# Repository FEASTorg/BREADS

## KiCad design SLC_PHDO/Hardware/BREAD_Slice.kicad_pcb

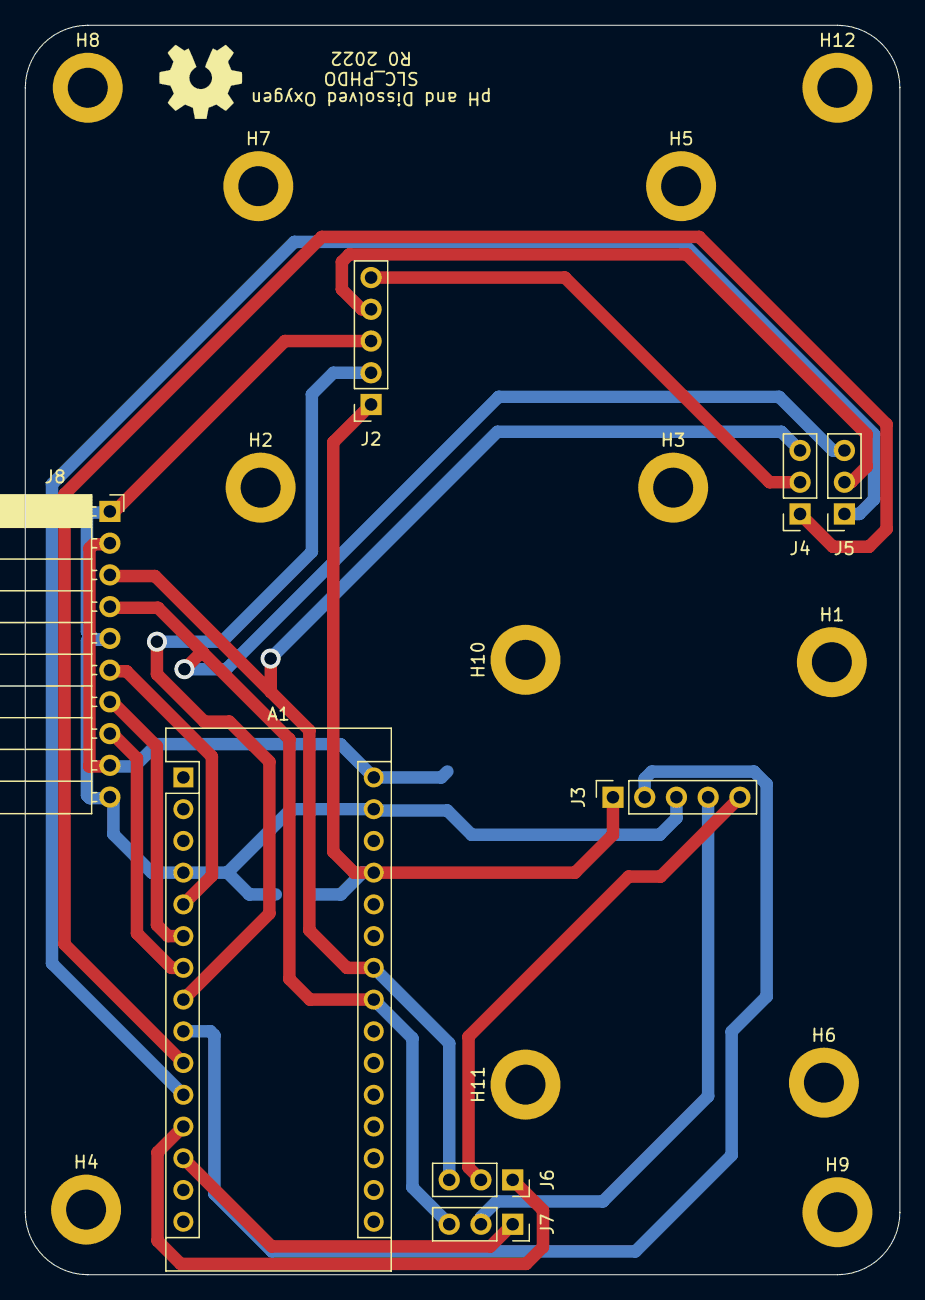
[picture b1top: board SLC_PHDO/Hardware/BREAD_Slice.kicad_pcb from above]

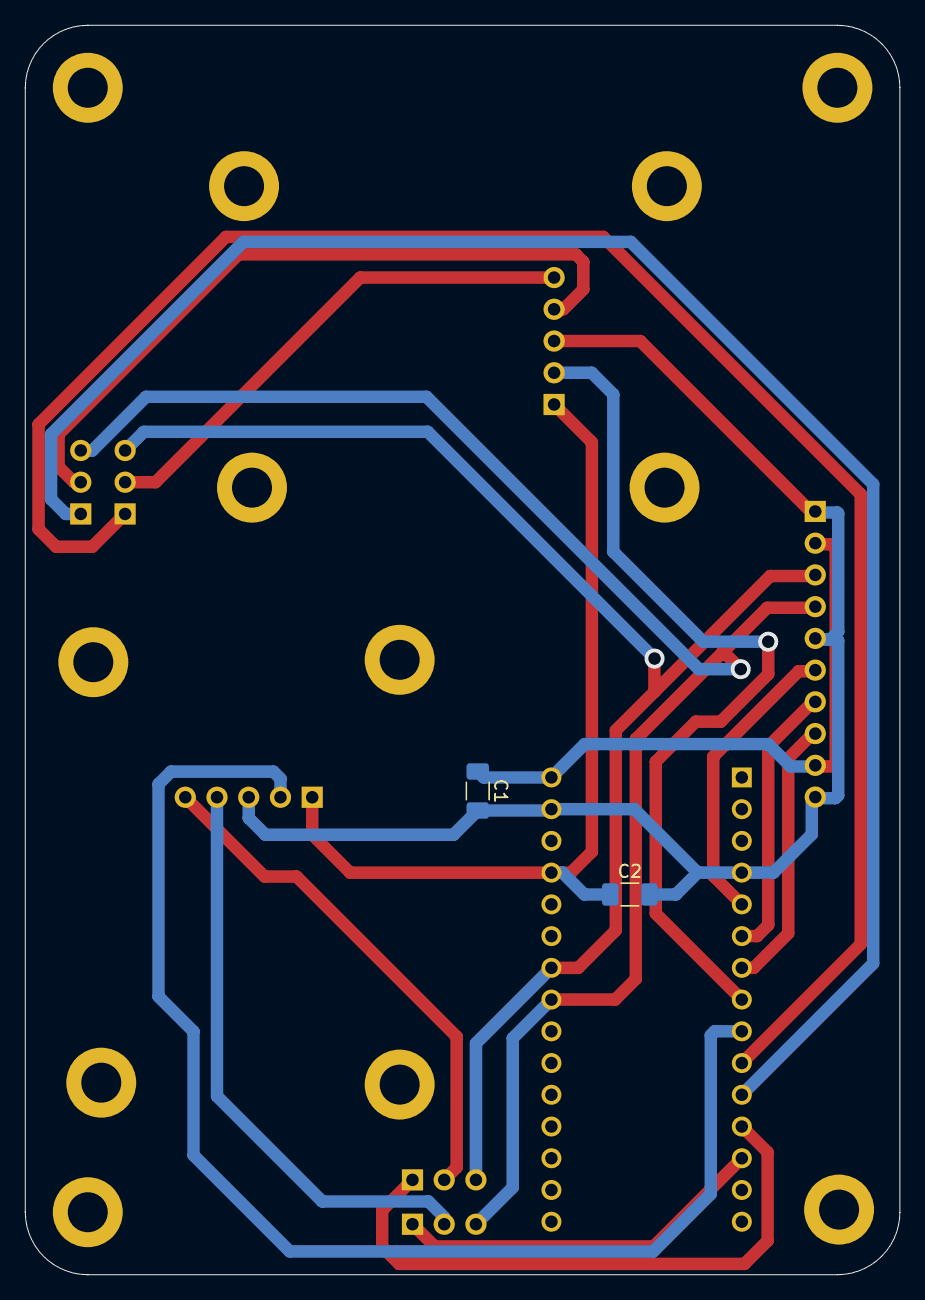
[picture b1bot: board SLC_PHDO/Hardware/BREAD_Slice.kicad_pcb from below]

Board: 2 copper layers, 70.0 x 100.0 mm, 23 parts (2 on the bottom side), 15 nets.

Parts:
A1: Arduino_Nano_v3.x; Arduino_Nano
C1, C2: 10uF_t; C_1206_3216Metric_Pad1.33x1.80mm_HandSolder
H1, H2, H3, H4, H5, H6, H7, H8, H9, H10, H11, H12: MountingHole; MountingHole_3.2mm_M3_DIN965_Pad
J2, J3: Conn_01x05_Female; PinSocket_1x05_P2.54mm_Vertical
J4, J5, J6, J7: Conn_01x03_Male; PinSocket_1x03_P2.54mm_Vertical
J8: Conn_01x10_Female; PinSocket_1x10_P2.54mm_Horizontal
Logo1: Logo_Open_Hardware_Small; OSHW-Symbol_6.7x6mm_SilkScreen

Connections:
+5V: A1.27 (+5V), C2.1, J2.1, J3.1
+12V: A1.30 (VIN), C1.1, J8.2, J8.9
/I2C_CLK: A1.24 (A5), J4.3, J6.3
/I2C_DAT: A1.23 (A4), J5.3, J7.3
/OFFO2: A1.8 (D5), J2.2
/OFFpH: A1.9 (D6), J3.2
/RX1: A1.10 (D7), J4.1
/RX1/SCL: J2.5, J4.2
/RX2: A1.12 (D9), J6.1
/RX2/SCL: J3.5, J6.2
/TX1: A1.11 (D8), J5.1
/TX1/SDA: J2.4, J5.2
/TX2: A1.13 (D10), J7.1
/TX2/SDA: J3.4, J7.2
GND: A1.4 (GND), A1.29 (GND), C1.2, C2.2, J2.3, J3.3, J8.1, J8.5, J8.10

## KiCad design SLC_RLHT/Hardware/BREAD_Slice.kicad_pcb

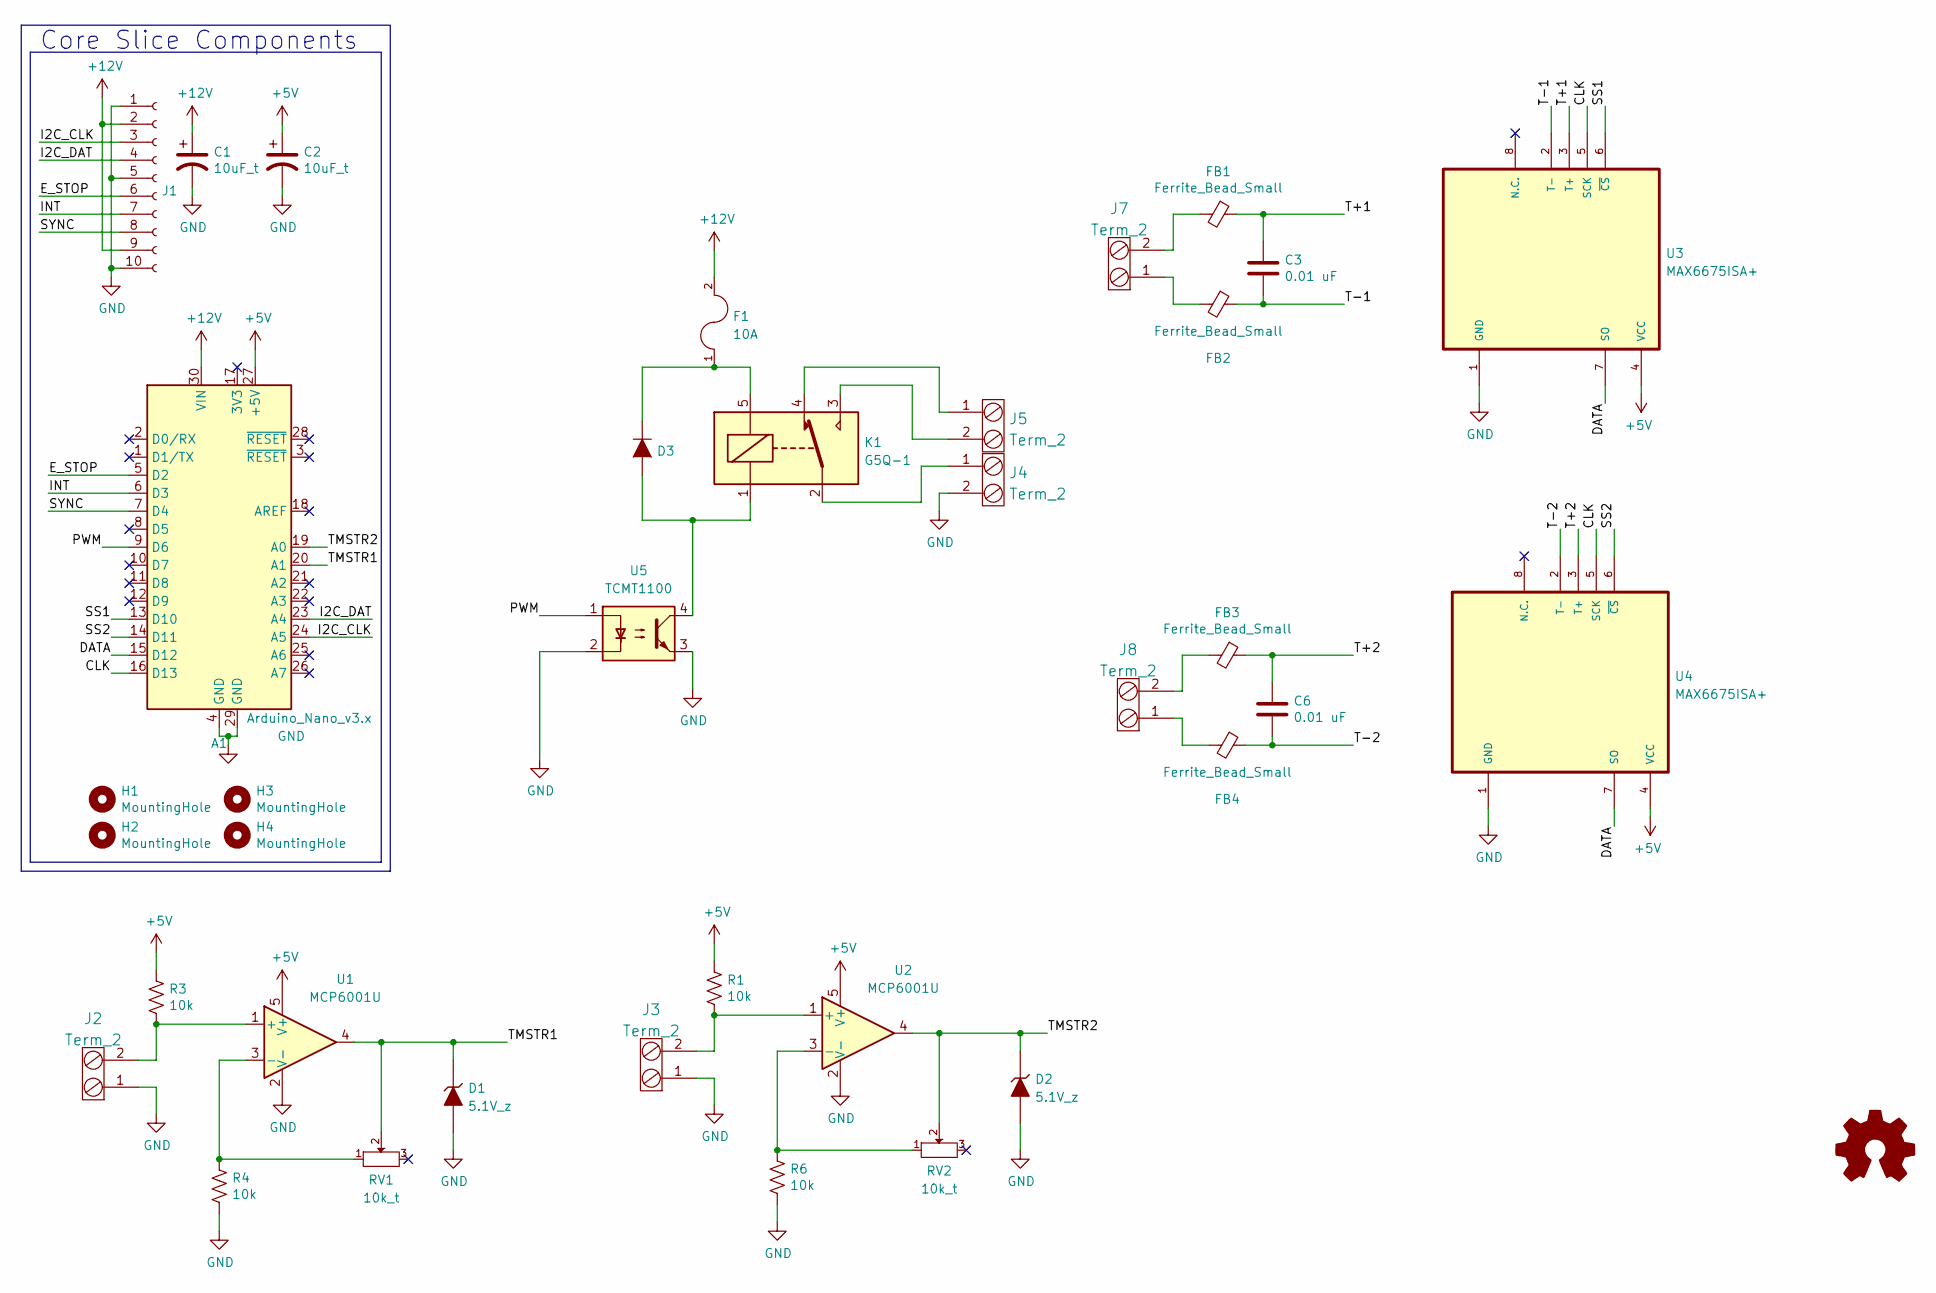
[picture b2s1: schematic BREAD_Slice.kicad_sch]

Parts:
A1: Arduino_Nano_v3.x; Arduino_Nano
C1, C2: 10uF_t; C_1206_HandSoldering; Part # T491C106K025AT
C3, C6: 0.01 uF; C_1206_HandSoldering
D1, D2: 5.1V_z; Diode_DO-41_SOD81_Horizontal_RM10; Part # 1N4733ATR
D3: General_Purpose_Diode; Diode_DO-201AD_Horizontal_RM15; Part # 1N914BWS
F1: 10A; Fuse_Holder; Part # 3522-2
FB1, FB2, FB3, FB4: Ferrite_Bead_Small; R_1206_HandSoldering
H1, H2, H3, H4: MountingHole; MountingHole_3.2mm_M3_DIN965_Pad
J1: Conn_01x10_Female; PinSocket_1x10_P2.54mm_Horizontal
J2, J3, J4, J5, J7, J8: Term_2; TerminalBlock_Pheonix_MKDS1.5-2pol; Part # 1935161
K1: G5Q-1; Relay_SPDT_Omron-G5Q-1
Logo1: Logo_Open_Hardware_Small; OSHW-Symbol_6.7x6mm_SilkScreen
R1, R3, R4, R6: 10k; R_1206_HandSoldering
RV1, RV2: 10k_t; Potentiometer_Bourns_3296W_3-8Zoll_Inline_ScrewUp; Part # 1-1623849-0
U1, U2: MCP6001U; SOT-23-5
U3, U4: MAX6675ISA+; SOIC127P600X175-8N
U5: TCMT1100; SOP-4_4.4x2.6mm_P1.27mm

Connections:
+5V: A1.27 (+5V), C2.1, R1.1, R3.1, U1.5 (V+), U2.5 (V+), U3.4 (VCC), U4.4 (VCC)
+12V: A1.30 (VIN), C1.1, F1.2, J1.2, J1.9
/CLK: A1.16 (D13), U3.5 (SCK), U4.5 (SCK)
/DATA: A1.15 (D12), U3.7 (SO), U4.7 (SO)
/E_STOP: A1.5 (D2), J1.6
/I2C_CLK: A1.24 (A5), J1.3
/I2C_DAT: A1.23 (A4), J1.4
/INT: A1.6 (D3), J1.7
/PWM: A1.9 (D6), U5.1
/SS1: A1.13 (D10), U3.6 (~CS)
/SS2: A1.14 (D11), U4.6 (~CS)
/SYNC: A1.7 (D4), J1.8
/T+1: C3.1, FB1.1, U3.3 (T+)
/T+2: C6.1, FB3.1, U4.3 (T+)
/T-1: C3.2, FB2.1, U3.2 (T-)
/T-2: C6.2, FB4.1, U4.2 (T-)
/TMSTR1: A1.20 (A1), D1.1 (K), RV1.2, U1.4
/TMSTR2: A1.19 (A0), D2.1 (K), RV2.2, U2.4
GND: A1.4 (GND), A1.29 (GND), C1.2, C2.2, D1.2 (A), D2.2 (A), J1.1, J1.5, J1.10, J2.1, J3.1, J4.2, R4.2, R6.2, U1.2 (V-), U2.2 (V-), U3.1 (GND), U4.1 (GND), U5.2, U5.3
unnamed: D3.1 (K), F1.1, K1.5
unnamed: FB1.2, J7.2
unnamed: FB2.2, J7.1
unnamed: FB3.2, J8.2
unnamed: FB4.2, J8.1
unnamed: J2.2, R3.2, U1.1 (+)
unnamed: J3.2, R1.2, U2.1 (+)
unnamed: J4.1, K1.2
unnamed: J5.1, K1.4
unnamed: J5.2, K1.3
unnamed: D3.2 (A), K1.1, U5.4
unnamed: R4.1, RV1.1, U1.3 (-)
unnamed: R6.1, RV2.1, U2.3 (-)

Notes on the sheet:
Core Slice Components

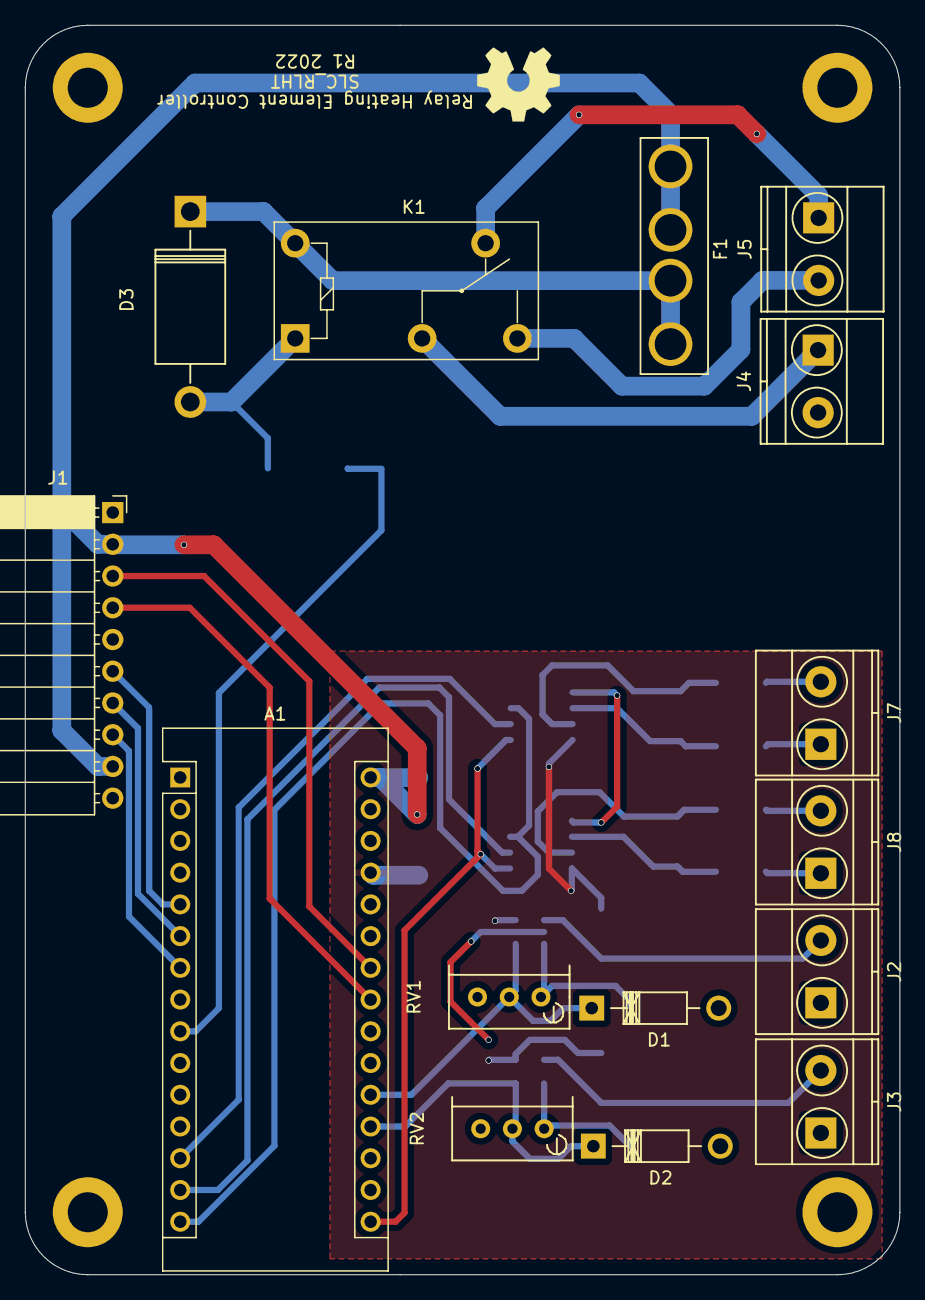
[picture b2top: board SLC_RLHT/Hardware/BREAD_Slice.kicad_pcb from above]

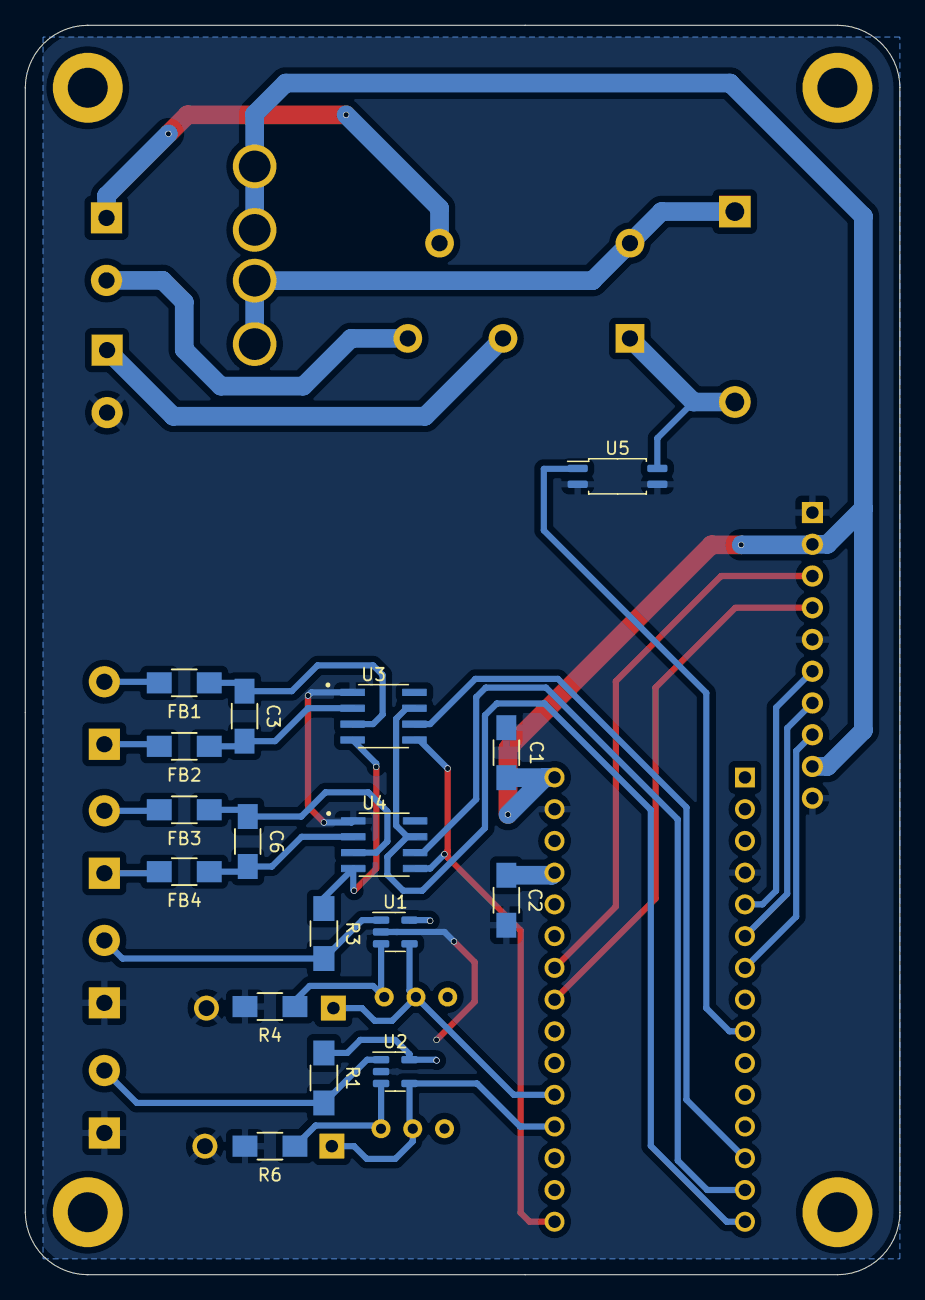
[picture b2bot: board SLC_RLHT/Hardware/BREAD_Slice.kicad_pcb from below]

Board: 2 copper layers, 70.0 x 100.0 mm, 37 parts (17 on the bottom side), 32 nets.

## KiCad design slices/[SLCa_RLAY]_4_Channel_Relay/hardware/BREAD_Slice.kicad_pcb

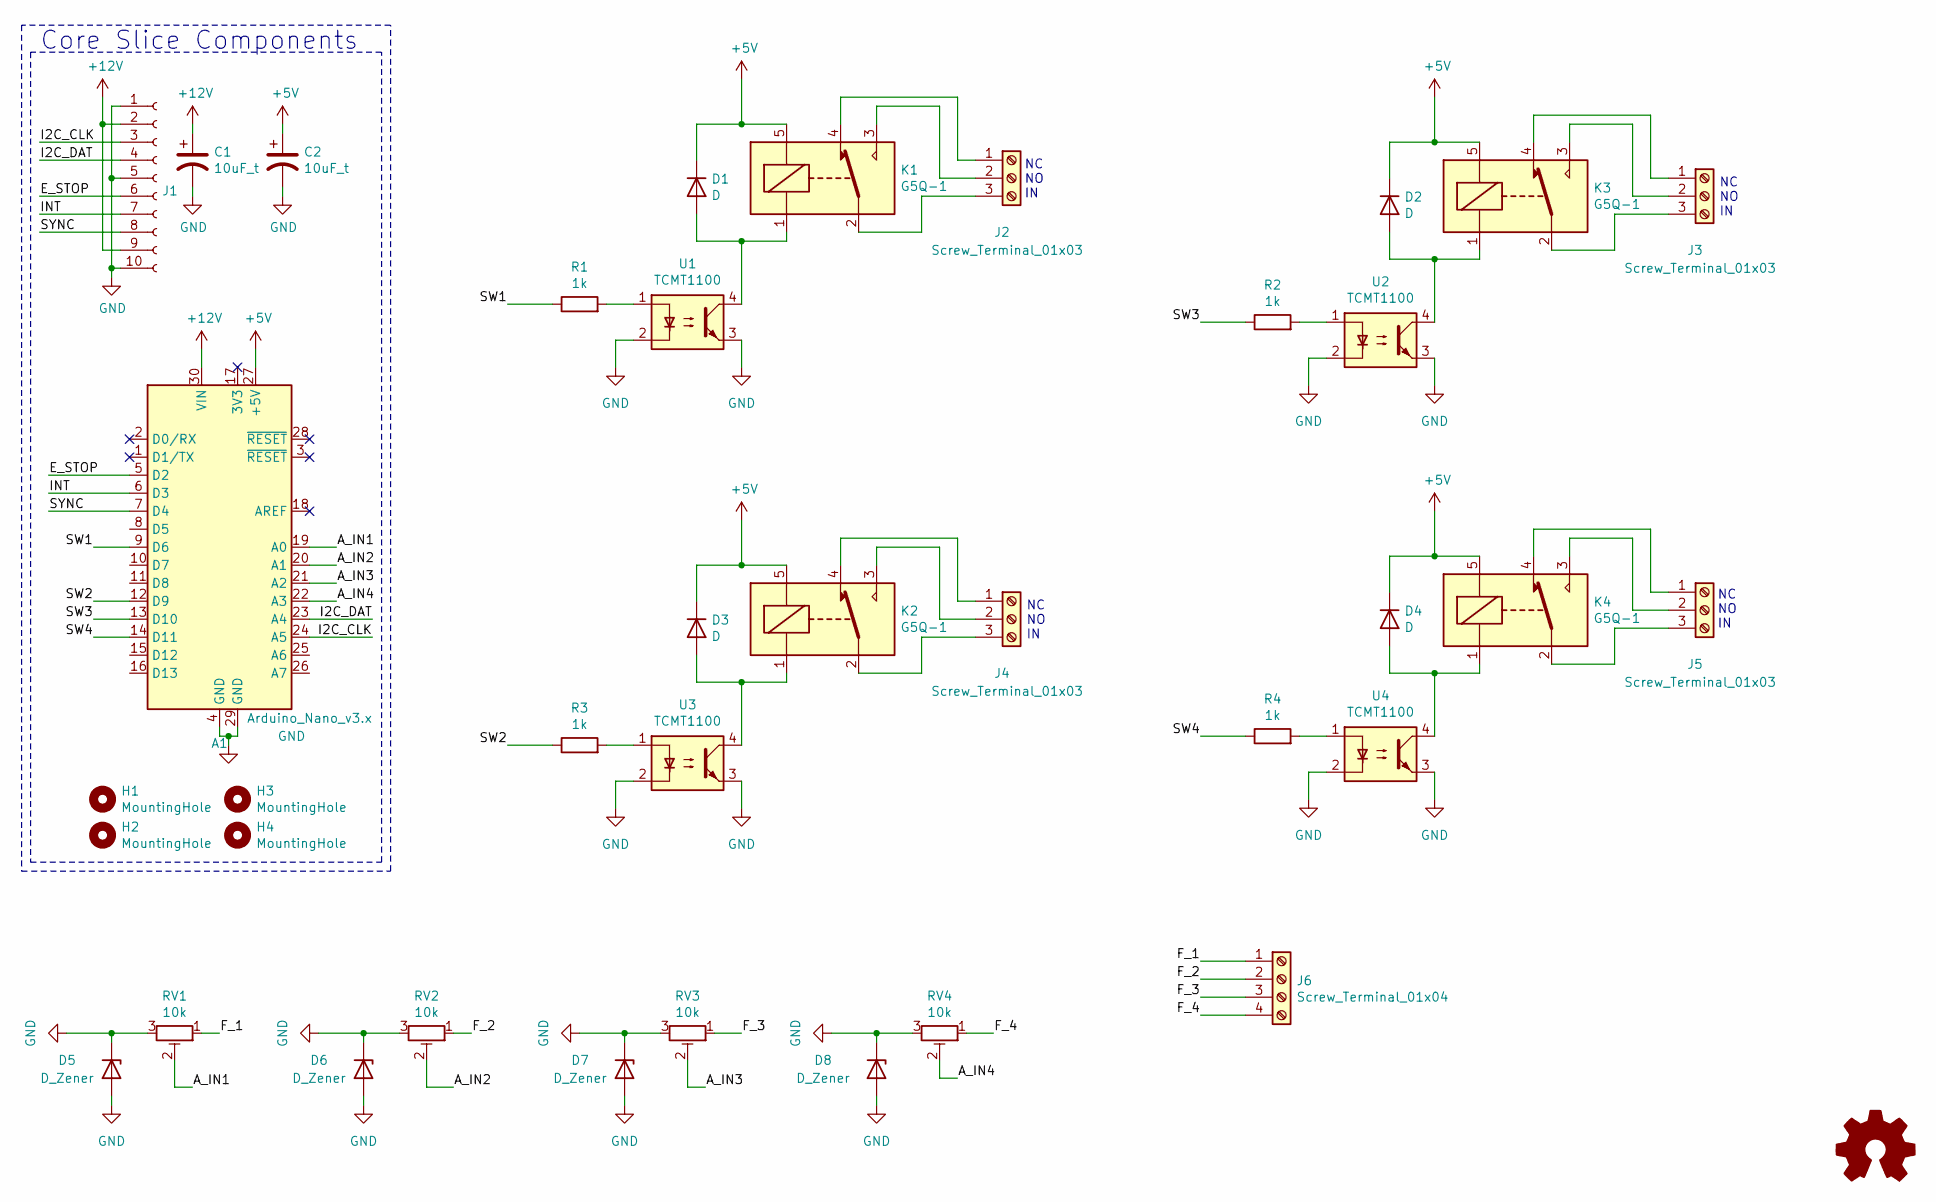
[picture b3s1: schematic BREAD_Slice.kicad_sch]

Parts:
A1: Arduino_Nano_v3.x; Arduino_Nano
C1, C2: 10uF_t; C_2312; Part # T491C106K025AT
D1, D2, D3, D4: D; D_1206_3216Metric_Pad1.42x1.75mm_HandSolder
D5, D6, D7, D8: D_Zener; D_1206_3216Metric_Pad1.42x1.75mm_HandSolder
H1, H2, H3, H4: MountingHole; MountingHole_3.2mm_M3_DIN965_Pad
J1: Conn_01x10_Female; PinSocket_1x10_P2.54mm_Horizontal
J2, J3, J4, J5: Screw_Terminal_01x03; TerminalBlock_TE_282834-3_1x03_P2.54mm_Horizontal
J6: Screw_Terminal_01x04; TerminalBlock_TE_282834-4_1x04_P2.54mm_Horizontal
K1, K2, K3, K4: G5Q-1; Relay_SPDT_Omron-G5Q-1
Logo1: Logo_Open_Hardware_Small; OSHW-Symbol_6.7x6mm_SilkScreen
R1, R2, R3, R4: 1k; R_1206_3216Metric_Pad1.30x1.75mm_HandSolder
RV1, RV2, RV3, RV4: 10k; Potentiometer_Bourns_3266W_Vertical
U1, U2, U3, U4: TCMT1100; SOP-4_4.4x2.6mm_P1.27mm

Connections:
+5V: A1.27 (+5V), C2.1, D1.1 (K), D2.1 (K), D3.1 (K), D4.1 (K), K1.5, K2.5, K3.5, K4.5
+12V: A1.30 (VIN), C1.1, J1.2, J1.9
/A_IN1: A1.19 (A0), RV1.2
/A_IN2: A1.20 (A1), RV2.2
/A_IN3: A1.21 (A2), RV3.2
/A_IN4: A1.22 (A3), RV4.2
/E_STOP: A1.5 (D2), J1.6
/F_1: J6.1, RV1.1
/F_2: J6.2, RV2.1
/F_3: J6.3, RV3.1
/F_4: J6.4, RV4.1
/I2C_CLK: A1.24 (A5), J1.3
/I2C_DAT: A1.23 (A4), J1.4
/INT: A1.6 (D3), J1.7
/SW1: A1.9 (D6), R1.1
/SW2: A1.12 (D9), R3.1
/SW3: A1.13 (D10), R2.1
/SW4: A1.14 (D11), R4.1
/SYNC: A1.7 (D4), J1.8
GND: A1.4 (GND), A1.29 (GND), C1.2, C2.2, D5.1 (K), D5.2 (A), D6.1 (K), D6.2 (A), D7.1 (K), D7.2 (A), D8.1 (K), D8.2 (A), J1.1, J1.5, J1.10, RV1.3, RV2.3, RV3.3, RV4.3, U1.2, U1.3, U2.2, U2.3, U3.2, U3.3, U4.2, U4.3
unnamed: D1.2 (A), K1.1, U1.4
unnamed: D2.2 (A), K3.1, U2.4
unnamed: D3.2 (A), K2.1, U3.4
unnamed: D4.2 (A), K4.1, U4.4
unnamed: J2.1, K1.4
unnamed: J2.2, K1.3
unnamed: J2.3, K1.2
unnamed: J3.1, K3.4
unnamed: J3.2, K3.3
unnamed: J3.3, K3.2
unnamed: J4.1, K2.4
unnamed: J4.2, K2.3
unnamed: J4.3, K2.2
unnamed: J5.1, K4.4
unnamed: J5.2, K4.3
unnamed: J5.3, K4.2
unnamed: R1.2, U1.1
unnamed: R2.2, U2.1
unnamed: R3.2, U3.1
unnamed: R4.2, U4.1

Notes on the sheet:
NC NO IN
Core Slice Components

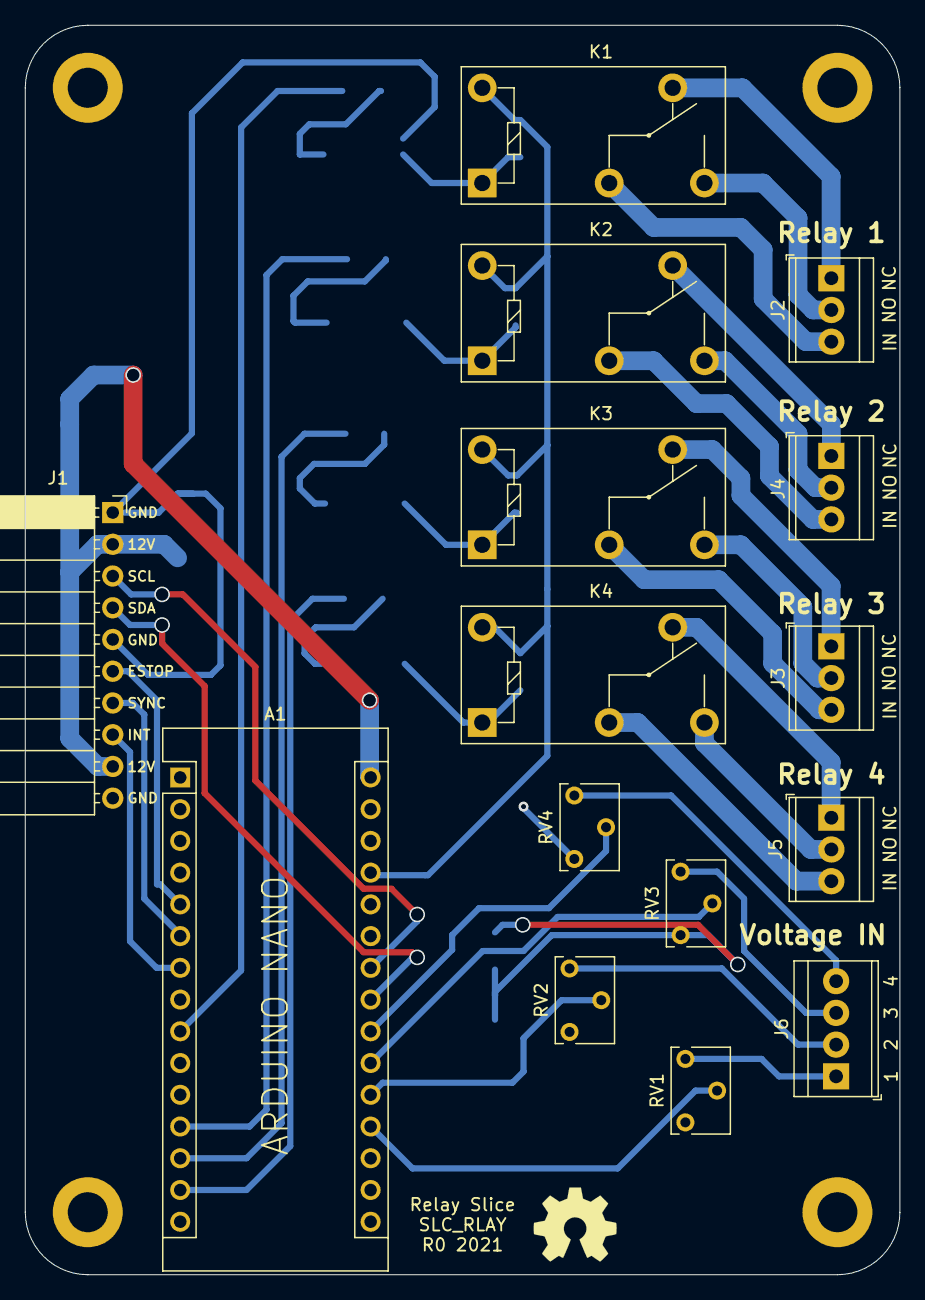
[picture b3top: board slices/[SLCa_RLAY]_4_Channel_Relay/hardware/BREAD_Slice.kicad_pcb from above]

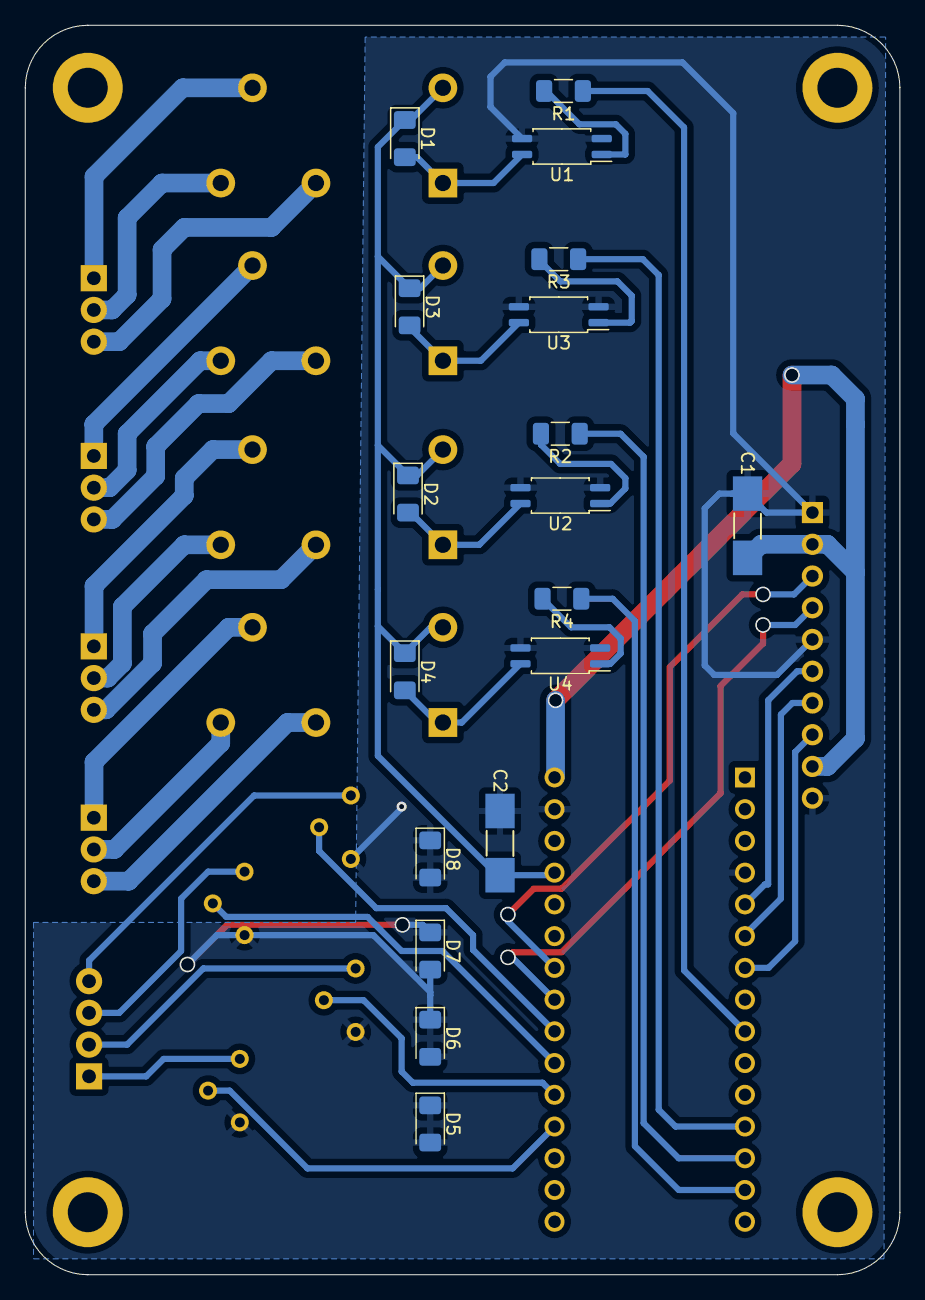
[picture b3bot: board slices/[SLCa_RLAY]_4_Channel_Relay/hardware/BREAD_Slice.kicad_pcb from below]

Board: 2 copper layers, 70.0 x 100.0 mm, 38 parts (18 on the bottom side), 40 nets.

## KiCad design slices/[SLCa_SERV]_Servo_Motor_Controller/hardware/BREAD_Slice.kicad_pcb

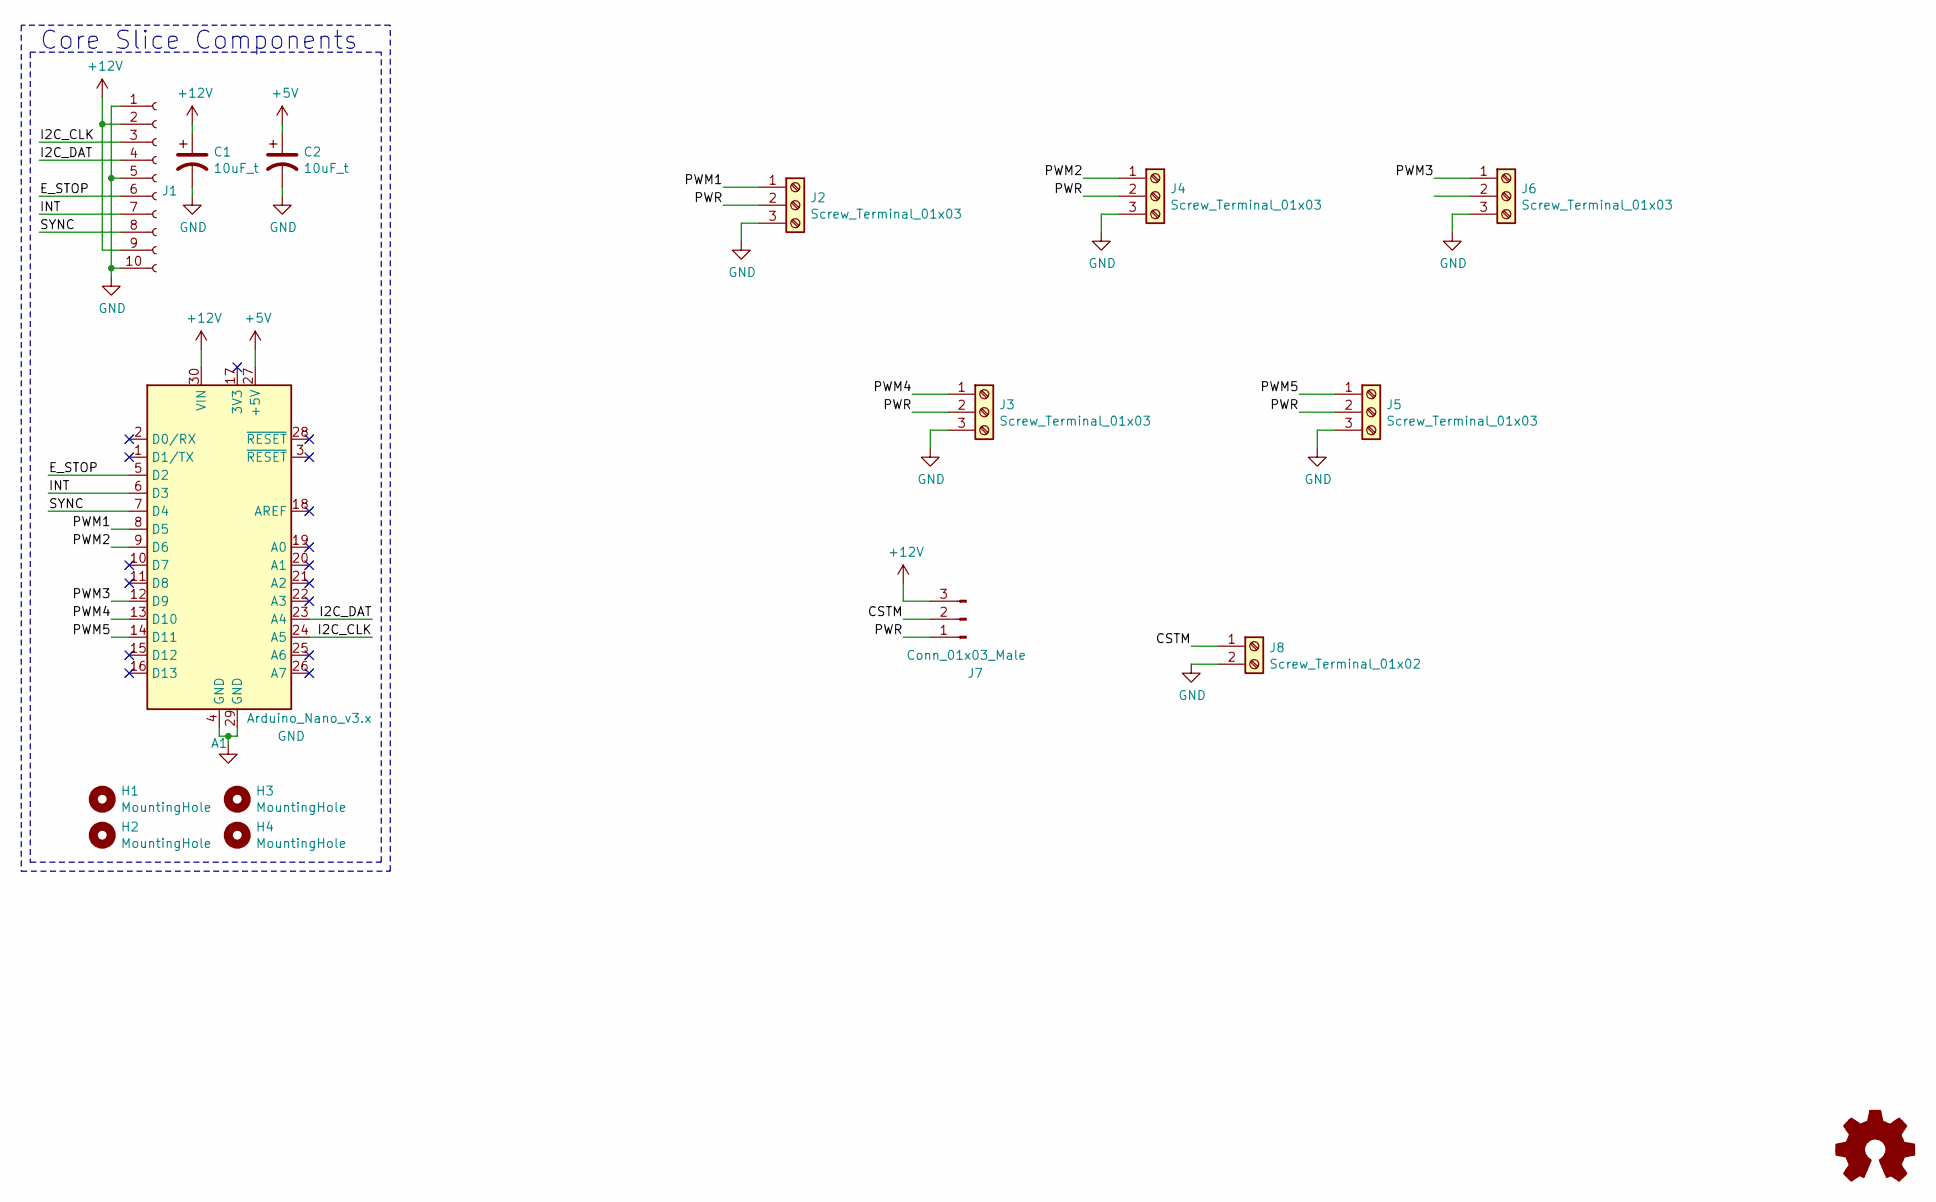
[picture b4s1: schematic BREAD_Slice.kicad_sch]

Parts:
A1: Arduino_Nano_v3.x; Arduino_Nano
C1, C2: 10uF_t; C_2312; Part # T491C106K025AT
H1, H2, H3, H4: MountingHole; MountingHole_3.2mm_M3_DIN965_Pad
J1: Conn_01x10_Female; PinSocket_1x10_P2.54mm_Horizontal
J2, J3, J4, J5, J6: Screw_Terminal_01x03; TerminalBlock_TE_282834-3_1x03_P2.54mm_Horizontal
J7: Conn_01x03_Male; PinSocket_1x03_P2.54mm_Vertical
J8: Screw_Terminal_01x02; TerminalBlock_TE_282834-2_1x02_P2.54mm_Horizontal
Logo1: Logo_Open_Hardware_Small; OSHW-Symbol_6.7x6mm_SilkScreen

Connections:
+5V: A1.27 (+5V), C2.1
+12V: A1.30 (VIN), C1.1, J1.2, J1.9, J7.3
/CSTM: J7.2, J8.1
/E_STOP: A1.5 (D2), J1.6
/I2C_CLK: A1.24 (A5), J1.3
/I2C_DAT: A1.23 (A4), J1.4
/INT: A1.6 (D3), J1.7
/PWM1: A1.8 (D5), J2.1
/PWM2: A1.9 (D6), J4.1
/PWM3: A1.12 (D9), J6.1
/PWM4: A1.13 (D10), J3.1
/PWM5: A1.14 (D11), J5.1
/PWR: J2.2, J3.2, J4.2, J5.2, J7.1
/SYNC: A1.7 (D4), J1.8
GND: A1.4 (GND), A1.29 (GND), C1.2, C2.2, J1.1, J1.5, J1.10, J2.3, J3.3, J4.3, J5.3, J6.3, J8.2

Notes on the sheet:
Core Slice Components

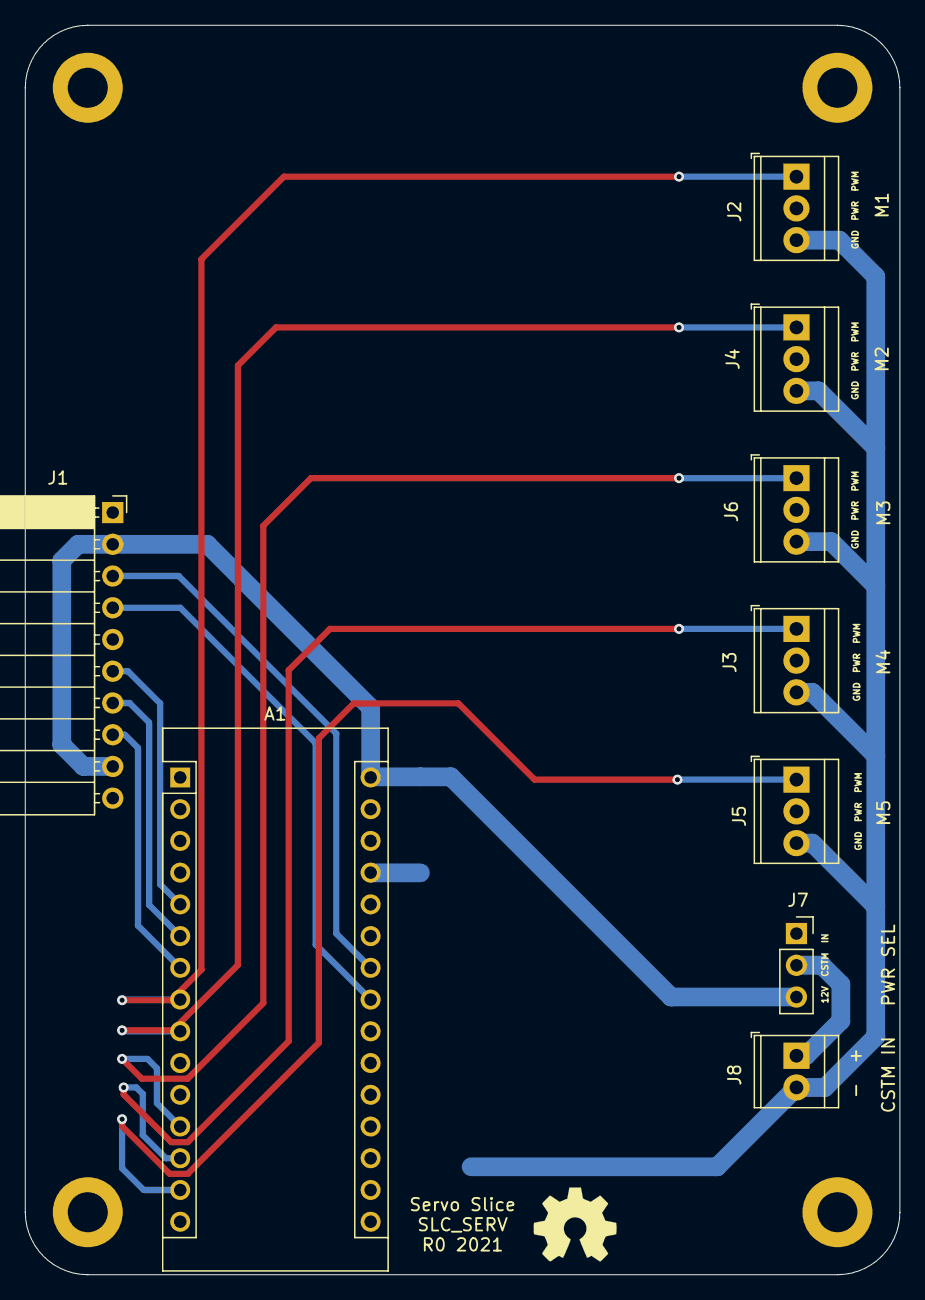
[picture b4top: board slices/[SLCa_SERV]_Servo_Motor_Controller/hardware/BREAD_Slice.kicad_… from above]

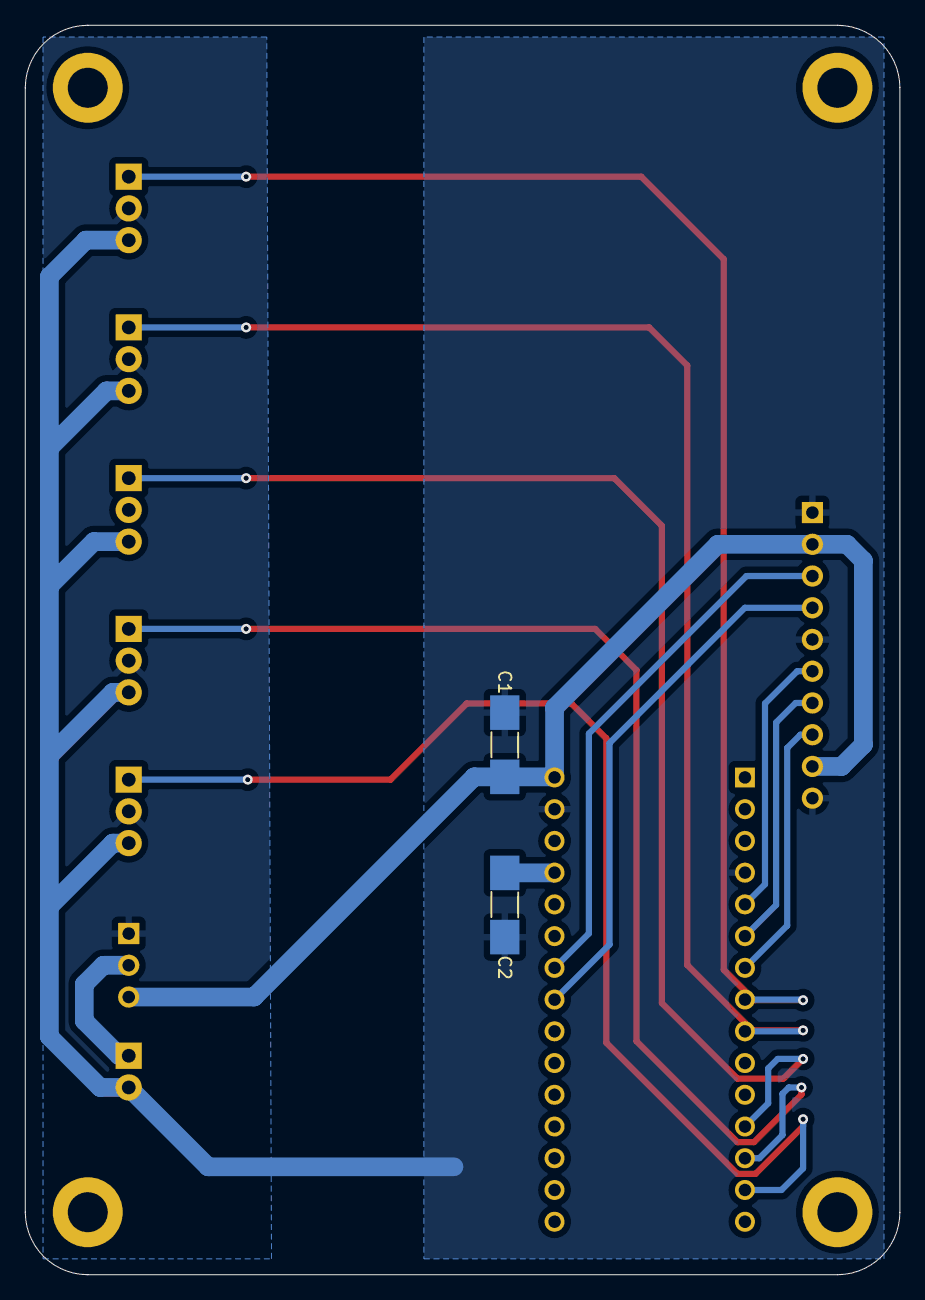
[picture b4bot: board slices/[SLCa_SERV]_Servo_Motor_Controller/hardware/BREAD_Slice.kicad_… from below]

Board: 2 copper layers, 70.0 x 100.0 mm, 16 parts (2 on the bottom side), 15 nets.
